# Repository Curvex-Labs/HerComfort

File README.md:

# HerComfort

HerComfort is a wearable menstrual comfort and wellness solution designed to support women during emergencies, disasters, displacement, travel, relief-camp conditions, and other situations where access to conventional menstrual-care resources may be limited. During floods, earthquakes, evacuation, temporary shelters, or other emergency situations, women may have limited access to hot water, private resting spaces, continuous healthcare support, or convenient methods for managing menstrual discomfort. HerComfort aims to provide a portable, rechargeable, hands-free solution that combines controlled heating, vibration-based comfort, physiological monitoring, and local therapy control in a compact wearable belt.

The system integrates temperature monitoring, muscle-activity sensing, motion and posture awareness, BLE connectivity, and offline operation so that essential comfort functions can remain available even when continuous smartphone or internet access is not practical.
By combining wearable therapy, sensing, portability, and connected monitoring, HerComfort is intended to improve menstrual comfort, independence, and dignity for women in both everyday life and challenging emergency or disaster-response environments.

---

<p align="center">
  <b>HerComfort Physical Prototype with Live Mobile Monitoring</b>
</p>

---

## Project Overview

HerComfort is being developed as an integrated wearable platform intended to support:

- Controlled heating therapy
- Vibration therapy
- EMG-based muscle activity monitoring
- Motion and posture sensing
- Temperature monitoring
- BLE connectivity
- Offline therapy control
- SOS / emergency support
- Battery-powered wearable operation

The final system is being designed around a compact custom PCB housed inside the curved front enclosure.

---

## Mechanical CAD Design

The refined HerComfort mechanical design was created in SolidWorks with a curved front therapy module, adjustable elastic belt, integrated controls, charging access, rear comfort surface, and dry EMG contact placement.

### Main Mechanical Dimensions

| Feature | Nominal Design |
|---|---|
| Therapy module | 185 mm long × 78 mm high |
| Maximum loft width | Approximately 80.1 mm |
| Overall depth envelope | Approximately 21.4 mm |
| Rear abdominal curvature | Approximately 3.5 mm sag across 160 mm |
| Rear comfort pad | Approximately 2.4 mm modeled section |
| Elastic strap | 48 mm wide × 3 mm thick |
| Charging opening | 10 × 3.8 mm USB-C access recess |
| Dry EMG contacts | Three 18 mm circular pads |
| EMG spacing | 30 mm center-to-center |
| Wearable circumference shown | Approximately 830 mm |

---

## Main CAD Views

### Front and Rear

### Isometric and Inner View

---

## EMG Contact Design

HerComfort includes three dry EMG contact points on the skin-facing inner side of the belt.

The contacts are designed as:

- 18 mm circular metallic pads
- Arranged in one row
- 30 mm center-to-center spacing
- Positioned near the front-right inner belt region
- Integrated into the wearable surface

The intended signal chain is:

**Dry EMG electrodes → Muscle BioAmp Candy → Signal conditioning → ESP32-C6 ADC**

---

## Electronics Development

HerComfort currently uses a custom KiCad-designed carrier PCB that integrates the existing prototype modules into a compact and serviceable wearable electronics platform.

The present carrier board interfaces:

- Seeed Studio XIAO ESP32C6
- MPU6050 IMU
- Muscle BioAmp Candy
- DS18B20 temperature sensor
- TP4056 charging module
- Mini-360 DC-DC converter
- Heating pad
- Vibration motor
- AO3400A MOSFET switching stages
- Physical Mode button
- Li-ion battery

This carrier board represents the current functional prototype electronics.

A future fully integrated HerComfort PCB is planned to replace the removable modules with dedicated onboard circuitry and additional safety, sensing, power-management, and protection features.

---

## PCB Carrier Board

A custom HerComfort carrier PCB has been designed in KiCad to replace loose prototype wiring and provide a cleaner, compact hardware platform for the current working electronics.

The carrier board supports:

- Seeed Studio XIAO ESP32C6
- MPU6050 IMU
- Muscle BioAmp Candy
- DS18B20 temperature sensor
- TP4056 Li-ion charging module
- Mini-360 DC-DC converter
- AO3400A MOSFET heater control
- AO3400A MOSFET vibration motor control
- 1N5819 flyback protection diode
- Mode push button
- Heating pad connection
- Vibration motor connection
- Li-ion battery connection

The removable modules are mounted using female headers so that the controller and sensor modules can be replaced or serviced without replacing the complete PCB.
Images/PCB_Images/PCB_Back.png
### PCB Schematic

### PCB Front and Back Views

### PCB Routing

### Main GPIO Mapping

| Function | XIAO Pin | ESP32-C6 GPIO |
|---|---:|---:|
| Mode Button | D0 | GPIO0 |
| EMG Signal | D1 | GPIO1 |
| I²C SDA | D4 | GPIO22 |
| I²C SCL | D5 | GPIO23 |
| Vibration Motor | D7 | GPIO17 |
| DS18B20 Temperature | D8 | GPIO19 |
| Heating Pad | D10 | GPIO18 |

### Power Architecture

```text
3.7 V Li-ion Battery
        │
        ▼
      TP4056
        │
        ├────────► XIAO ESP32C6 battery input
        │
        ▼
     Mini-360
        │
        ▼
 Regulated therapy rail
        │
        ├────────► Heating Pad
        │
        └────────► Vibration Motor

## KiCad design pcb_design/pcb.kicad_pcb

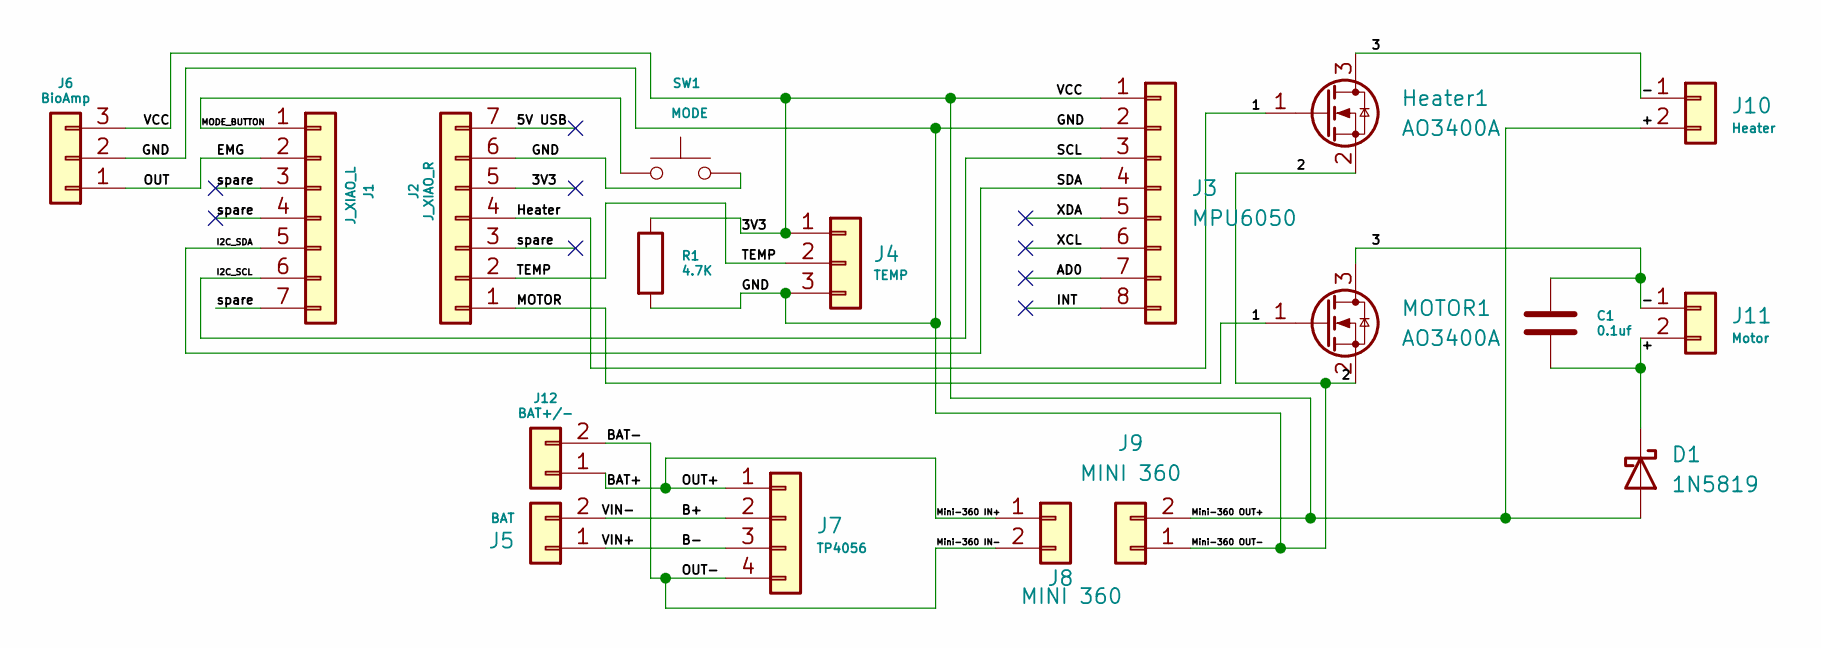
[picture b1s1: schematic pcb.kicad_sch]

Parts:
C1: 0.1uf; C_0805_2012Metric
D1: 1N5819; D_DO-41_SOD81_P10.16mm_Horizontal
Heater1: AO3400A; SOT-23
J1: J_XIAO_L; PinSocket_1x07_P2.54mm_Vertical
J2: J_XIAO_R; PinSocket_1x07_P2.54mm_Vertical
J3: MPU6050; PinHeader_1x08_P2.54mm_Vertical
J4: TEMP; PinSocket_1x03_P2.54mm_Vertical
J5: BAT; PinHeader_1x02_P2.54mm_Vertical
J6: BioAmp; PinSocket_1x03_P2.54mm_Vertical
J7: TP4056; PinHeader_1x04_P2.54mm_Vertical
J8, J9: MINI 360; PinHeader_1x02_P2.54mm_Vertical
J10: Heater; PinHeader_1x02_P2.54mm_Vertical
J11: Motor; PinHeader_1x02_P2.54mm_Vertical
J12: BAT+/-; PinHeader_1x02_P2.54mm_Vertical
MOTOR1: AO3400A; SOT-23
R1: 4.7K; R_0805_2012Metric
SW1: MODE; PinSocket_1x02_P2.54mm_Vertical

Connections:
/1: Heater1.1 (G), J2.1, J2.4, MOTOR1.1 (G)
/2: Heater1.2 (S), J2.6, J3.2, J4.3, J6.2, J9.1, MOTOR1.2 (S), R1.2, SW1.2
/5V USB: J2.7
/+: C1.1, D1.1 (K), D1.2 (A), J2.5, J3.1, J4.1, J6.3, J9.2, J10.2, J11.2, R1.1
/-: C1.2, Heater1.3 (D), J10.1, J11.1, MOTOR1.3 (D)
/AD0: J3.7
/B+: J5.2, J7.2
/B-: J5.1, J7.3
/BAT+: J7.1, J8.1, J12.1
/BAT-: J7.4, J8.2, J12.2
/EMG: J1.2, J6.1
/I2C_SCL: J1.6, J3.3
/I2C_SDA: J1.5, J3.4
/INT: J3.8
/MODE_BUTTON: J1.1, SW1.1
/TEMP: J2.2, J4.2
/XCL: J3.6
/XDA: J3.5
/spare: J1.3, J1.4, J1.7, J2.3

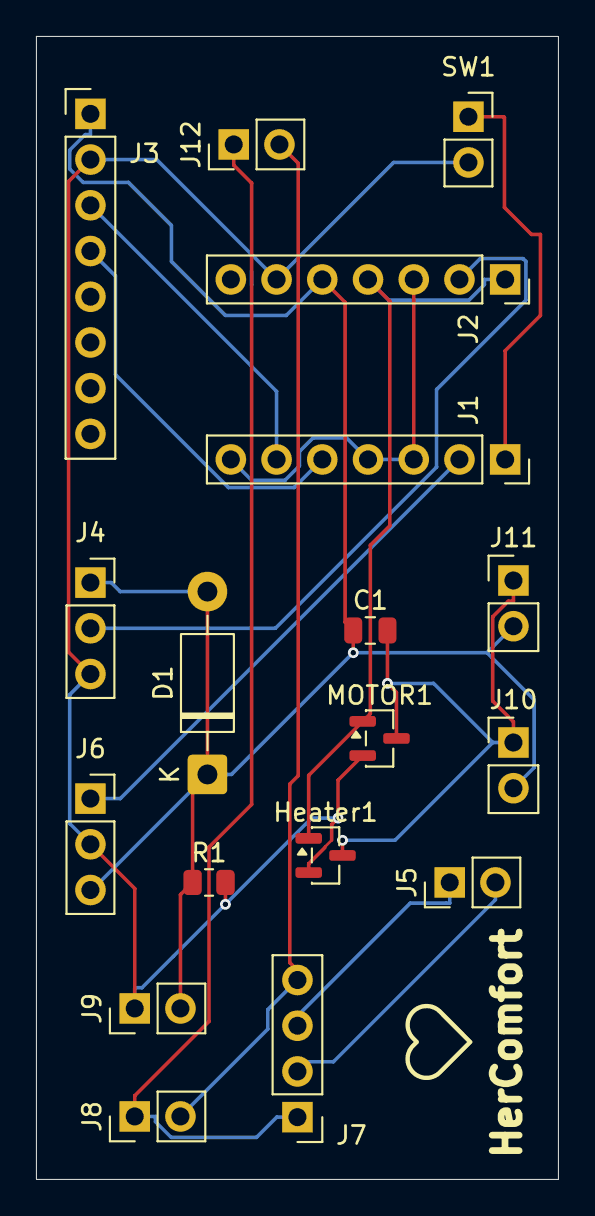
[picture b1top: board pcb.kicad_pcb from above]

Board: 2 copper layers, 29.0 x 63.5 mm, 18 parts (0 on the bottom side), 14 nets.
